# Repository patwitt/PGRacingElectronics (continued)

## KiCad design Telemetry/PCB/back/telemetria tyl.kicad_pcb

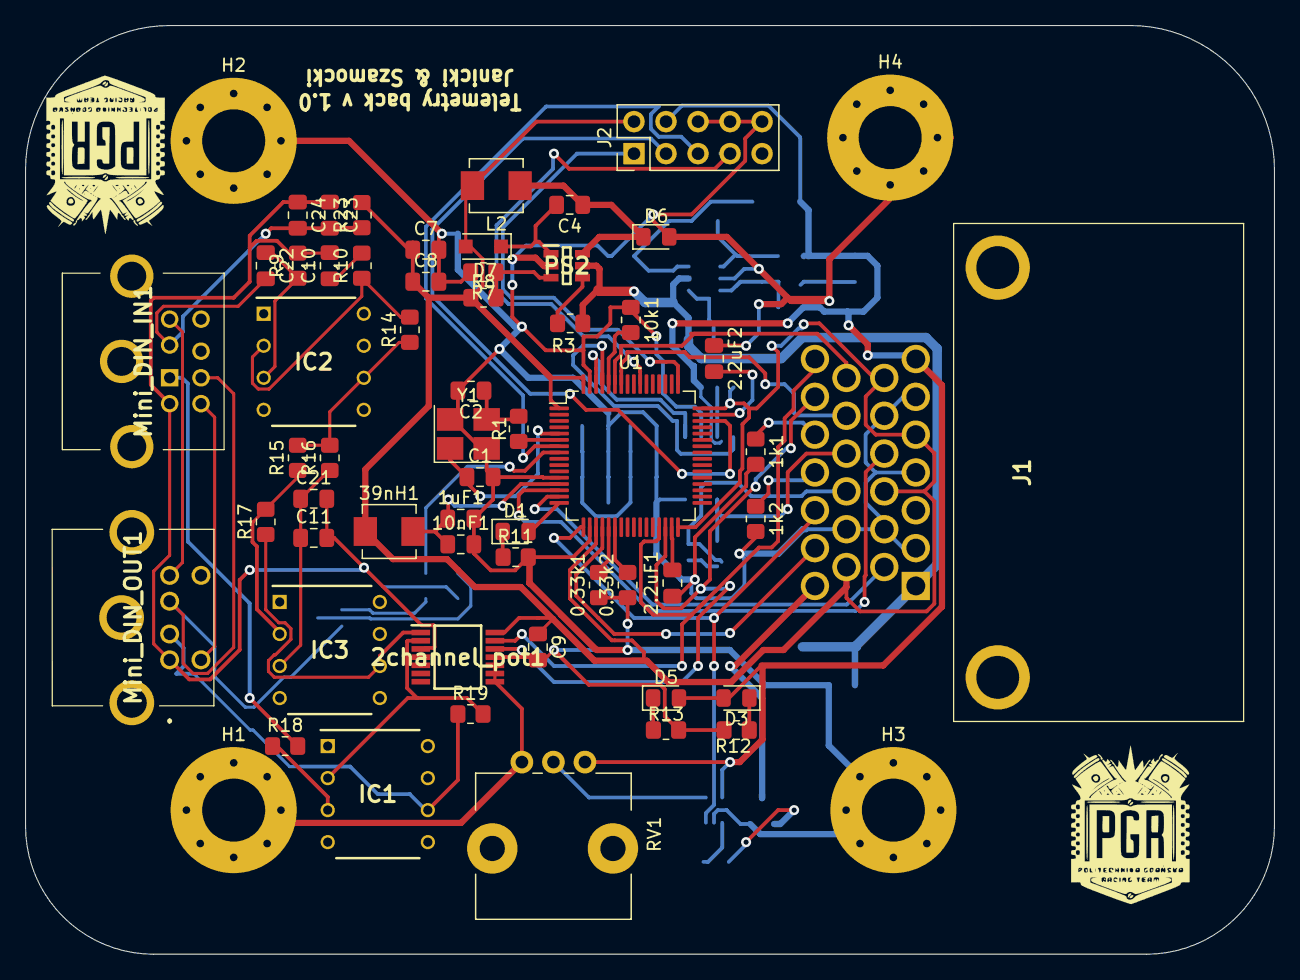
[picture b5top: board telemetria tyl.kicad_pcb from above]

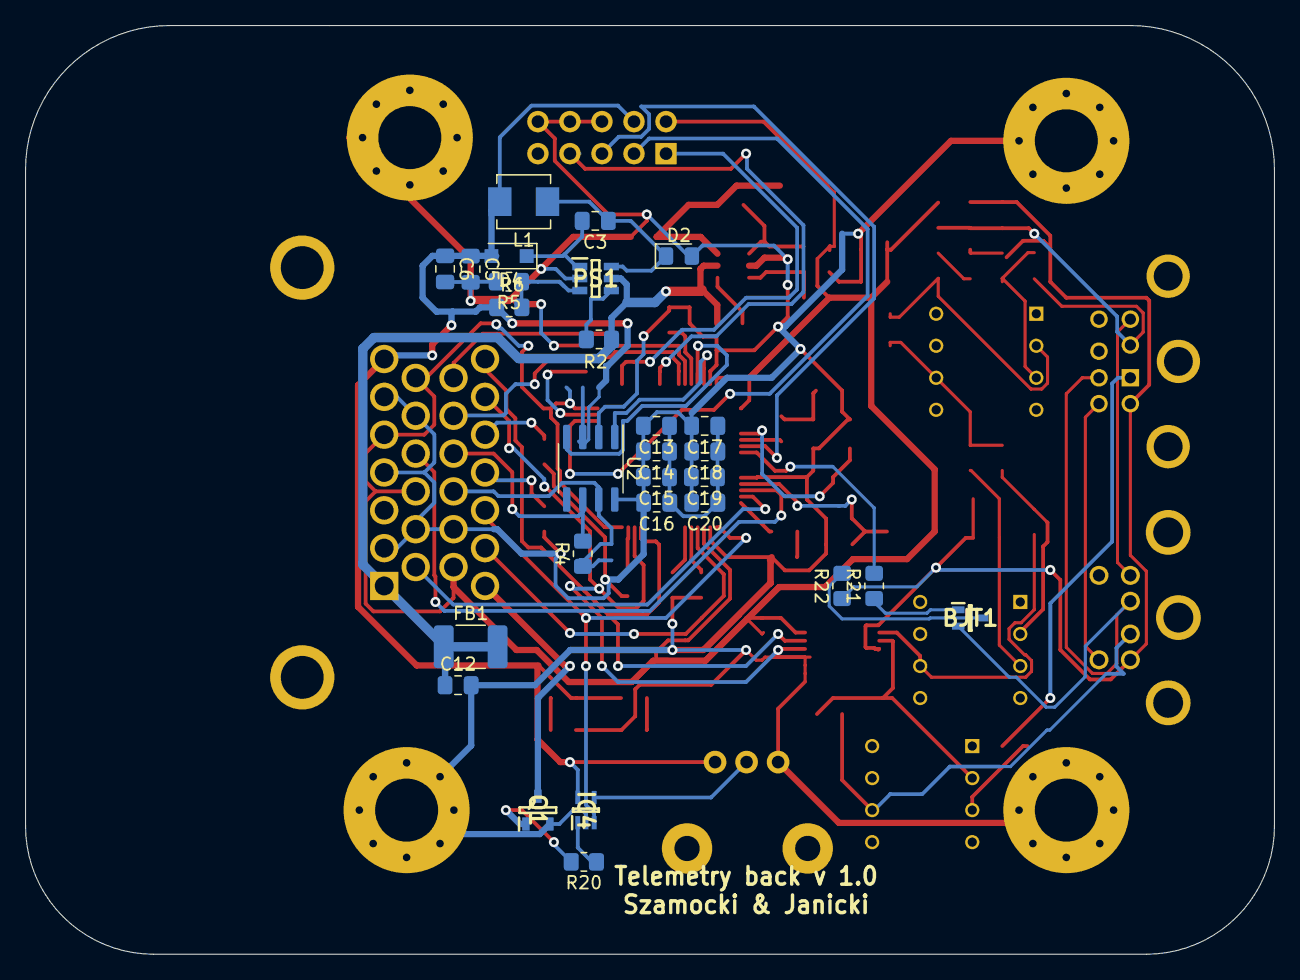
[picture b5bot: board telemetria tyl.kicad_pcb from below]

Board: 2 copper layers, 99.1 x 73.7 mm, 88 parts (28 on the bottom side), 66 nets.

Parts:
0.33k1, 0.33k2, 1k1, 1k2, 10k1: R; R_0805_2012Metric_Pad1.20x1.40mm_HandSolder
1uF1, 10nF1: C1; C_0805_2012Metric_Pad1.18x1.45mm_HandSolder
2.2uF1, 2.2uF2: C_Small; C_0805_2012Metric_Pad1.18x1.45mm_HandSolder
2channel_pot1: MAX5478EUD+T; SOP65P640X110-14N
39nH1: 39nH; L_Vishay_IHLP-1616
BJT1: BC846BW,115; SOT65P210X110-3N
C1, C2: 1uF; C_0805_2012Metric_Pad1.18x1.45mm_HandSolder
C3, C4, C12, C13, C14, C15, C16, C17, C18, C19, C20: 100nF; C_0805_2012Metric_Pad1.18x1.45mm_HandSolder
C5, C6, C7, C8, C24: 10uF; C_0805_2012Metric_Pad1.18x1.45mm_HandSolder
C9: 0.1uF; C_0805_2012Metric_Pad1.18x1.45mm_HandSolder
C10, C11, C21, C22: C; C_0805_2012Metric_Pad1.18x1.45mm_HandSolder
C23: ?; C_0805_2012Metric_Pad1.18x1.45mm_HandSolder
D1, D3, D5: LED_5V; D_0805_2012Metric_Pad1.15x1.40mm_HandSolder
D2, D6: D_Schottky; D_0805_2012Metric_Pad1.15x1.40mm_HandSolder
D4, D7: 1N4148; D_SOD-123F
FB1: Ferrite_Bead; C_1812_4532Metric_Pad1.57x3.40mm_HandSolder
H1, H2, H3, H4: MountingHole_Pad; MountingHole_5mm_Pad_Via
IC1, IC2, IC3: LM741CN_NOPB; DIP794W53P254L959H508Q8N
IC4: NCX2200GW,125; NCX2200GW
J1: Conn_01x26_Male; 64734231
J2: Conn_02x05_Odd_Even; PinHeader_2x05_P2.54mm_Vertical
L1, L2: 10uH; L_Vishay_IHLP-1616
Mini_DIN_IN1: 5749268-1; 57492681
Mini_DIN_OUT1: 5750071-1; 57500711
PS1, PS2: MP2359DT-LF-P; SOT95P280X145-6N
Q1: PMV280ENEAR
R1: R_Small; R_0805_2012Metric_Pad1.20x1.40mm_HandSolder
R2, R3: 100k; R_0805_2012Metric_Pad1.20x1.40mm_HandSolder
R4: 120; R_0805_2012Metric_Pad1.20x1.40mm_HandSolder
R5, R6, R7, R8, R10, R11, R12, R13, R14, R15, R16, R17, R18, R23: R; R_0805_2012Metric_Pad1.20x1.40mm_HandSolder
R9: 1M; R_0805_2012Metric_Pad1.20x1.40mm_HandSolder
R19: R?; R_0805_2012Metric_Pad1.20x1.40mm_HandSolder
R20: 3.3k; R_0805_2012Metric_Pad1.20x1.40mm_HandSolder
R21: 4.7k; R_0805_2012Metric_Pad1.20x1.40mm_HandSolder
R22: 1k; R_0805_2012Metric_Pad1.20x1.40mm_HandSolder
RV1: R_POT; Potentiometer_Alps_RK09L_Single_Vertical
U1: STM32F405RGTx; LQFP-64_10x10mm_P0.5mm
U2: MCP2561-E-SN; SOIC-8_3.9x4.9mm_P1.27mm
Y1: Crystal_GND24_Small; Crystal_SMD_3225-4Pin_3.2x2.5mm_HandSoldering

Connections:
12C1_SCL: J1.18, U1.58
12C2_SDA: 2channel_pot1.12, J1.21, U1.30
+3.3VA: 1uF1.1, 10nF1.1, 39nH1.2, U1.13
+3V3: 2channel_pot1.14, 39nH1.1, C7.1, C8.1, C9.1, C13.1, C14.1, C15.1, C16.1, C17.1, C18.1, C19.1, C20.1, D7.2, J1.5, J1.8, J1.11, J1.14, J2.2, L2.2, R8.1, R23.2, U1.1, U1.19, U1.32, U1.48, U1.64
+5V: C5.1, C6.1, D3.2, D4.2, D5.2, IC4.5, J1.7, J2.4, L1.2, R6.1, RV1.3, U2.3
+12V: C12.1, FB1.1, FB1.2, J1.1, PS1.5, PS2.5, R2.1, R3.1
ADC1_IN0_AMORKI: J1.10, U1.14
ADC2_IN1_AMORKI: J1.13, U1.15
BREAK_PRESSURE_0: IC4.3, J1.24, U1.17
BREAK_PRESSURE_ADC: J1.25, U1.20
CAN1_RX: U1.61, U2.4
CAN1_TX: U1.62, U2.1
CAN_H1: J1.16, R4.1, U2.7
CAN_L1: J1.17, R4.2, U2.6
GND: 0.33k1.1, 0.33k2.1, 1k1.2, 1k2.2, 1uF1.2, 2.2uF1.1, 2.2uF2.1, 2channel_pot1.8, 2channel_pot1.9, 2channel_pot1.10, 2channel_pot1.11, 10k1.1, 10nF1.2, C1.2, C2.2, C5.2, C6.2, C7.2, C8.2, C9.2, C12.2, C13.2, C14.2, C15.2, C16.2, C17.2, C18.2, C19.2, C20.2, D2.2, D6.2, H1.1, H2.1, H3.1, H4.1, IC4.2, J1.2, J1.4, J1.6, J1.9, J1.12, J1.15, J2.6, J2.8, J2.10, PS1.2, PS2.2, Q1.2, R5.2, R7.2, R11.2, R12.2, R13.2, RV1.1, U1.12, U1.18, U1.63, U2.2, U2.8, Y1.2, Y1.4
GND_MIC&ANC: 2channel_pot1.3, C10.2, C11.2, C21.2, C23.1, C24.1, Mini_DIN_IN1.3, Mini_DIN_OUT1.3, R9.2, R22.1
GND_SPK: BJT1.2, Mini_DIN_IN1.4, Mini_DIN_OUT1.2
I2C1_SDA: J1.19, U1.59
I2C2_SCL: 2channel_pot1.13, J1.20, U1.29
LED_GND: J1.26, Q1.3
LED_STATUS: D1.2, U1.16
NRST: J2.5, U1.7
unnamed: 2.2uF1.2, U1.31
unnamed: 2.2uF2.2, U1.47
unnamed: 2channel_pot1.1, IC3.6, R17.1
unnamed: 2channel_pot1.2, IC1.2, R19.2
unnamed: 10k1.2, U1.60
unnamed: BJT1.1, R21.1
unnamed: BJT1.3, R22.2
unnamed: C2.1, R1.2, Y1.3
unnamed: C3.1, D2.1, L1.1, PS1.6
unnamed: C3.2, D4.1, PS1.1
unnamed: C4.1, D6.1, L2.1, PS2.6
unnamed: C4.2, D7.1, PS2.1
unnamed: C10.1, R10.2
unnamed: C11.1, C21.1, IC3.3, R16.1
unnamed: C22.1, IC2.3, R9.1
unnamed: D1.1, R11.1
unnamed: D3.1, R12.1
unnamed: D5.1, R13.1
unnamed: IC1.3, R18.1
unnamed: IC2.2, R10.1, R14.2
unnamed: IC2.6, R14.1, R15.2, R16.2
unnamed: IC3.2, R15.1, R17.2
unnamed: IC4.1, R20.1
unnamed: IC4.4, RV1.2
unnamed: PS1.3, R5.1, R6.2
unnamed: PS1.4, R2.2
unnamed: PS2.3, R7.1, R8.2
unnamed: PS2.4, R3.2
unnamed: Q1.1, R20.2
PTT: R21.2, U1.8
RCC_OSC_IN: C1.1, U1.5, Y1.1
RCC_OSC_OUT: R1.1, U1.6
SPK+: Mini_DIN_IN1.5, Mini_DIN_OUT1.4
SWCLK: J2.1, U1.49
SWDIO: J2.3, U1.46
SWO: J2.7, U1.55
TIM2_ETR: 0.33k1.2, U1.21
TIM3_ETR: 0.33k2.2, U1.22
TX_DATA: Mini_DIN_IN1.6, Mini_DIN_OUT1.5
VSS_IN_1: 1k1.1, J1.22
VSS_IN_2: 1k2.1, J1.23
V_ANC: C22.2, C23.2, C24.2, Mini_DIN_IN1.2, R23.1
V_MIC: Mini_DIN_IN1.1, R18.2
V_OUT: IC1.6, Mini_DIN_OUT1.1, R19.1

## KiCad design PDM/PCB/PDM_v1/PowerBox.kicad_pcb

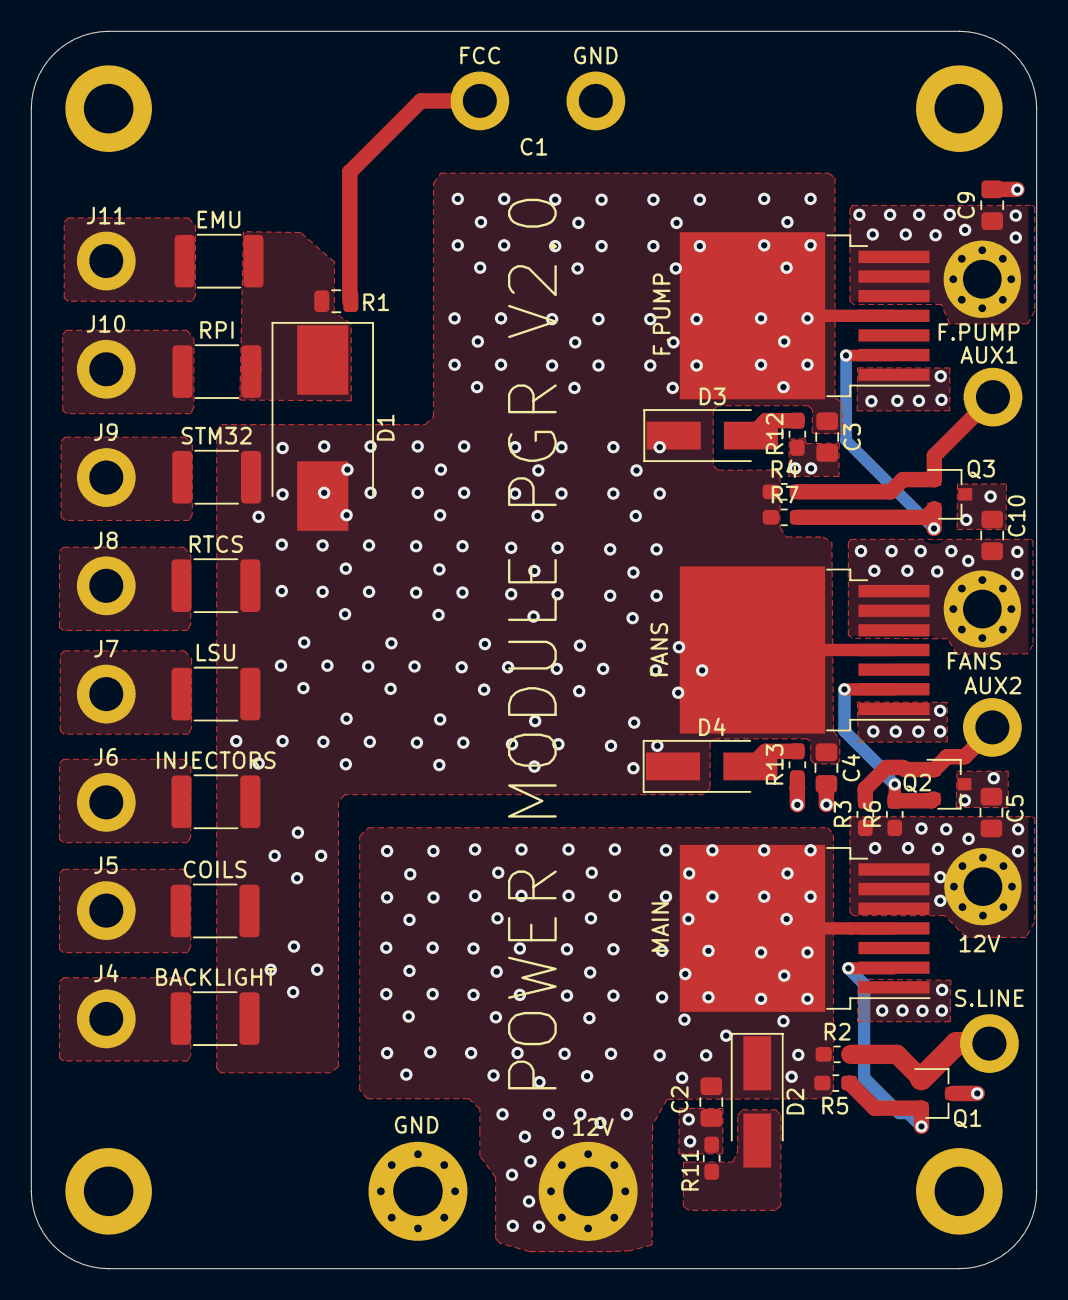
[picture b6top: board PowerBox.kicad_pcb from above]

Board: 4 copper layers, 65.0 x 80.0 mm, 55 parts (0 on the bottom side), 24 nets.

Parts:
12V: 85 K1 (starter); MountingHole_2.5mm_Pad_Via
AUX1: EMU PIN 21 GN(AUX1); MountingHole_2.2mm_M2_DIN965_Pad
AUX2: EMU PIN 13 GN (AUX2); MountingHole_2.2mm_M2_DIN965_Pad
BACKLIGHT: 2; Fuse_1812_4532Metric_Pad1.30x3.40mm_HandSolder
C1: 0.2F; Kondensator
C2, C3, C4: 100nF; C_0805_2012Metric_Pad1.15x1.40mm_HandSolder
C5, C9, C10: 10nF; C_0805_2012Metric_Pad1.15x1.40mm_HandSolder
COILS: 15; Fuse_1812_4532Metric_Pad1.30x3.40mm_HandSolder
D1: D; D_SMC_Handsoldering
D2, D3, D4: D_TVS_ALT; D_SMA_Handsoldering
EMU: 3; Fuse_1812_4532Metric_Pad1.30x3.40mm_HandSolder
F.PUMP: FUEL PUMP; MountingHole_2.5mm_Pad_Via
F.PUMP#2: BTS50010-1TAE; TO-263-7_TabPin4
FANS: FANS; MountingHole_2.5mm_Pad_Via
FANS#2: BTS50010-1TAE; TO-263-7_TabPin4
H1, H2, H3, H4: MountingHole; MountingHole_3.2mm_M3_DIN965_Pad
INJECTORS: 15; Fuse_1812_4532Metric_Pad1.30x3.40mm_HandSolder
J1: 12V BAT; MountingHole_3.2mm_M3_Pad_Via
J4: BACK LIGHT; MountingHole_2.2mm_M2_DIN965_Pad
J5: COILS; MountingHole_2.2mm_M2_DIN965_Pad
J6: INJECTORS; MountingHole_2.2mm_M2_DIN965_Pad
J7: LSU 4.9; MountingHole_2.2mm_M2_DIN965_Pad
J8: RACE TCS; MountingHole_2.2mm_M2_DIN965_Pad
J9: STM BOX; MountingHole_2.2mm_M2_DIN965_Pad
J10: RASPBERRY PI; MountingHole_2.2mm_M2_DIN965_Pad
J11: EMU; MountingHole_2.2mm_M2_DIN965_Pad
J16: GND; MountingHole_3.2mm_M3_Pad_Via
LSU: 3; Fuse_1812_4532Metric_Pad1.30x3.40mm_HandSolder
MAIN: BTS50010-1TAE; TO-263-7_TabPin4
Q1, Q2, Q3: Q_NPN_BCE; SOT-23
R1: 0.1; R_0805_2012Metric
R2, R3, R4: 22k; R_0603_1608Metric_Pad1.05x0.95mm_HandSolder
R5, R6, R7: 10k; R_0603_1608Metric_Pad1.05x0.95mm_HandSolder
R11, R12, R13: 1R; R_0603_1608Metric_Pad1.05x0.95mm_HandSolder
RPI: 5; Fuse_1812_4532Metric_Pad1.30x3.40mm_HandSolder
RTCS: Fuse; Fuse_1812_4532Metric_Pad1.30x3.40mm_HandSolder
S.LINE: SAFETY SYSTEM; MountingHole_2.2mm_M2_DIN965_Pad
STM32: 7.5; Fuse_1812_4532Metric_Pad1.30x3.40mm_HandSolder

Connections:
12V_BAT: C2.1, D2.1, J1.1, MAIN.4, R2.1, R5.1
12V_OUT1: 12V.1, BACKLIGHT.2, C3.1, C4.1, C5.1, COILS.2, D1.2, D3.1, D4.1, F.PUMP#2.4, FANS#2.4, INJECTORS.2, LSU.2, MAIN.5, MAIN.6, MAIN.7, R3.1, R4.1, R6.1, R7.1, RTCS.2, STM32.2
GND: C1.2, C2.2, C3.2, C4.2, C5.2, C9.2, C10.2, F.PUMP#2.1, FANS#2.1, J16.1, MAIN.1, Q1.3, Q2.3, Q3.3, R11.1, R12.1, R13.1
IN_1: MAIN.2, Q1.2, R5.2
IN_2: FANS#2.2, Q2.2, R6.2
IN_3: F.PUMP#2.2, Q3.2, R7.2
unnamed: C1.1, R1.2
unnamed: C9.1, F.PUMP.1, F.PUMP#2.5, F.PUMP#2.6, F.PUMP#2.7
unnamed: C10.1, FANS.1, FANS#2.5, FANS#2.6, FANS#2.7
unnamed: D1.1, EMU.2, R1.1, RPI.2
unnamed: D2.2, R11.2
unnamed: D3.2, R12.2
unnamed: D4.2, R13.2
unnamed: BACKLIGHT.1, J4.1
unnamed: COILS.1, J5.1
unnamed: INJECTORS.1, J6.1
unnamed: J7.1, LSU.1
unnamed: J8.1, RTCS.1
unnamed: J9.1, STM32.1
unnamed: J10.1, RPI.1
unnamed: EMU.1, J11.1
unnamed: AUX1.1, Q3.1, R4.2
unnamed: Q1.1, R2.2, S.LINE.1
unnamed: AUX2.1, Q2.1, R3.2

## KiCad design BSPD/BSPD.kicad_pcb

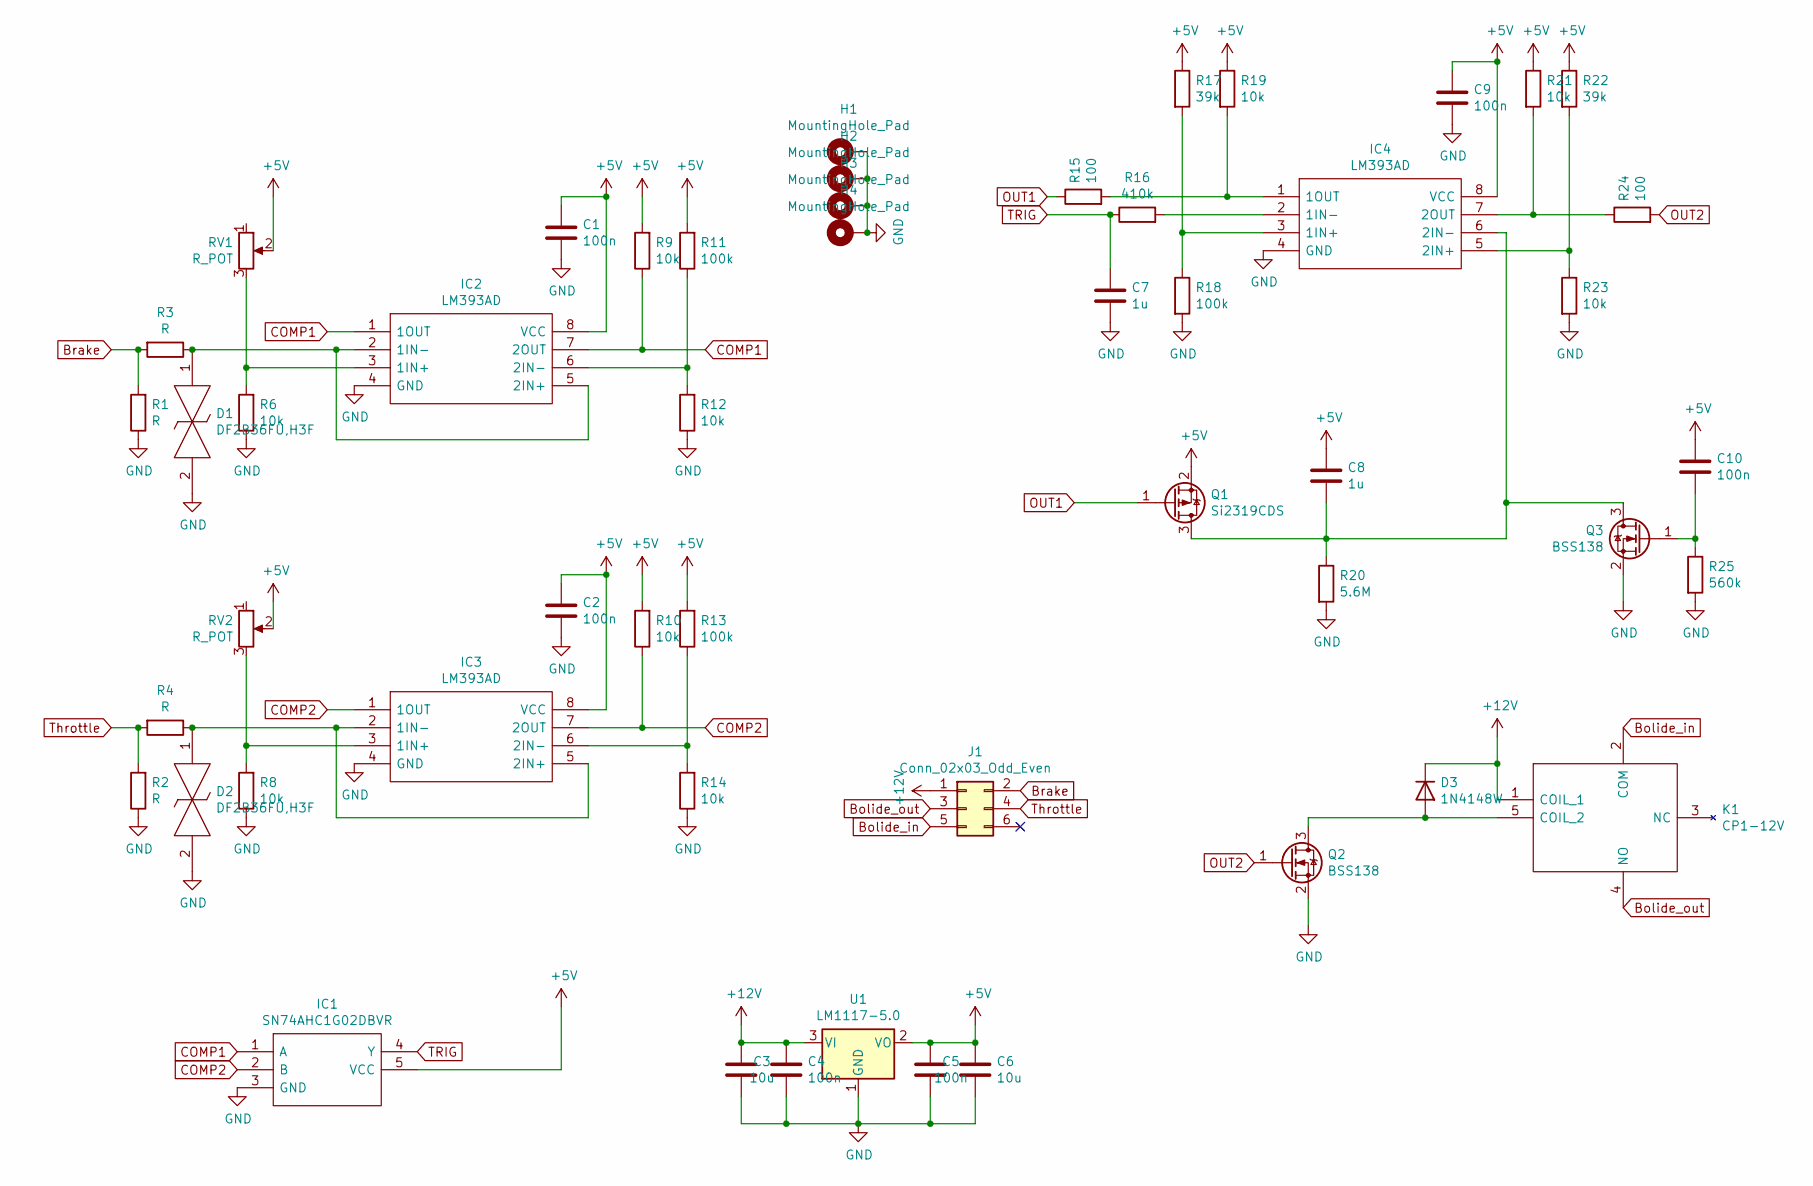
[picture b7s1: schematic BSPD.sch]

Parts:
C1, C2, C4, C5, C9, C10: 100n; C_0805_2012Metric
C3, C6: 10u; C_0805_2012Metric
C7, C8: 1u; C_0805_2012Metric
D1, D2: DF2B36FU,H3F; 1SS357TPH3F; Mouser Part Number 757-DF2B36FUH3F
D3: 1N4148W; D_SOD-123
H1, H2, H3, H4: MountingHole_Pad; MountingHole_2.2mm_M2_Pad_Via
IC1: SN74AHC1G02DBVR; SOT95P280X145-5N; Mouser Part Number 595-SN74AHC1G02DBVR
IC2, IC3, IC4: LM393AD; SOIC127P600X175-8N; Mouser Part Number 595-LM393AD
J1: Conn_02x03_Odd_Even; PinHeader_2x03_P2.54mm_Vertical
K1: CP1-12V; CP1FORMC_1; Mouser Part Number 769-CP1-12V
Q1: Si2319CDS; SOT-23
Q2, Q3: BSS138; SOT-23
R1, R2, R3, R4: R; R_0805_2012Metric
R6, R8, R9, R10, R12, R14, R19, R21, R23: 10k; R_0805_2012Metric
R11, R13, R18: 100k; R_0805_2012Metric
R15, R24: 100; R_0805_2012Metric
R16: 410k; R_0805_2012Metric
R17, R22: 39k; R_0805_2012Metric
R20: 5.6M; R_0805_2012Metric
R25: 560k; R_0805_2012Metric
RV1, RV2: R_POT; 64XK
U1: LM1117-5.0; SOT-223

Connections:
+5V: C1.1, C2.1, C5.1, C6.1, C8.1, C9.1, C10.1, IC1.5 (VCC), IC2.8 (VCC), IC3.8 (VCC), IC4.8 (VCC), Q1.2 (S), R9.2, R10.2, R11.2, R13.2, R17.1, R19.1, R21.1, R22.1, RV1.2, RV2.2, U1.2 (VO)
+12V: C3.1, C4.1, D3.1 (K), J1.1, K1.1 (COIL_1), U1.3 (VI)
Bolide_in: J1.5, K1.2 (COM)
Bolide_out: J1.3, K1.4 (NO)
Brake: J1.2, R1.2, R3.2
COMP1: IC1.1 (A), IC2.1 (1OUT), IC2.7 (2OUT), R9.1
COMP2: IC1.2 (B), IC3.1 (1OUT), IC3.7 (2OUT), R10.1
GND: C1.2, C2.2, C3.2, C4.2, C5.2, C6.2, C7.2, C9.2, D1.2, D2.2, H1.1, H2.1, H3.1, H4.1, IC1.3 (GND), IC2.4 (GND), IC3.4 (GND), IC4.4 (GND), Q2.2 (S), Q3.2 (S), R1.1, R2.1, R6.1, R8.1, R12.1, R14.1, R18.2, R20.2, R23.2, R25.2, U1.1 (GND)
unnamed: C8.2, IC4.6 (2IN-), Q1.3 (D), Q3.3 (D), R20.1
unnamed: C10.2, Q3.1 (G), R25.1
unnamed: D1.1, IC2.2 (1IN-), IC2.5 (2IN+), R3.1
unnamed: D2.1, IC3.2 (1IN-), IC3.5 (2IN+), R4.1
unnamed: D3.2 (A), K1.5 (COIL_2), Q2.3 (D)
unnamed: IC2.3 (1IN+), R6.2, RV1.3
unnamed: IC2.6 (2IN-), R11.1, R12.2
unnamed: IC3.3 (1IN+), R8.2, RV2.3
unnamed: IC3.6 (2IN-), R13.1, R14.2
unnamed: IC4.1 (1OUT), R15.2, R19.2
unnamed: IC4.2 (1IN-), R16.2
unnamed: IC4.3 (1IN+), R17.2, R18.1
unnamed: IC4.5 (2IN+), R22.2, R23.1
unnamed: IC4.7 (2OUT), R21.2, R24.1
OUT1: Q1.1 (G), R15.1
OUT2: Q2.1 (G), R24.2
TRIG: C7.1, IC1.4 (Y), R16.1
Throttle: J1.4, R2.2, R4.2

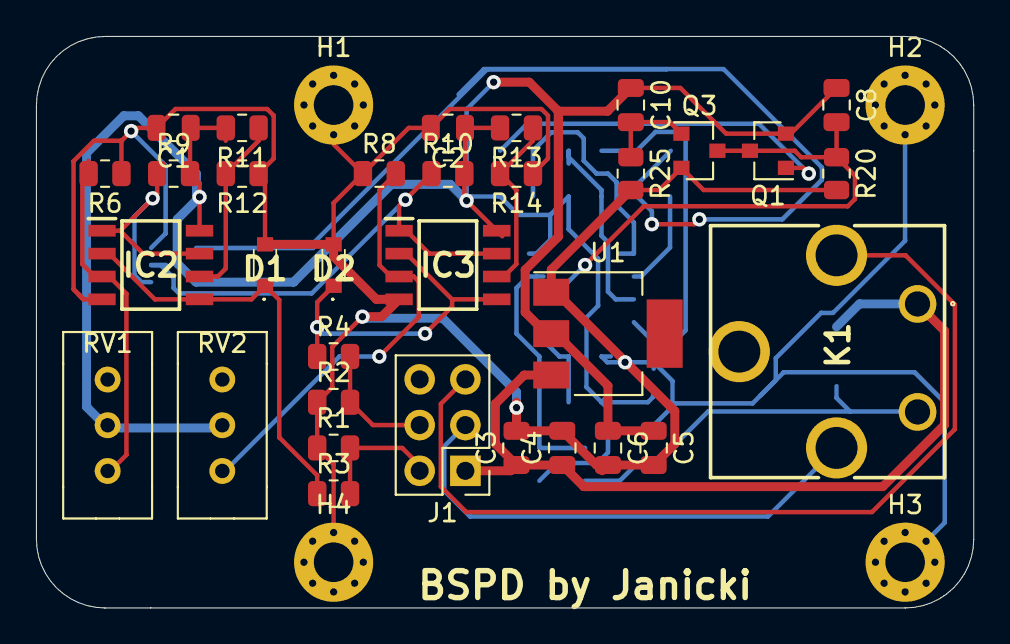
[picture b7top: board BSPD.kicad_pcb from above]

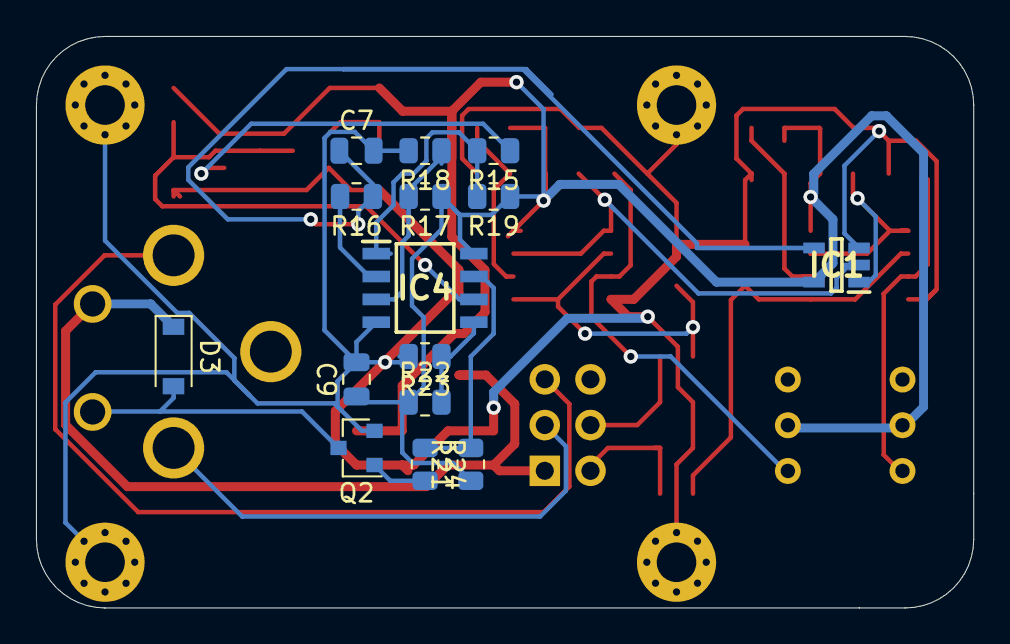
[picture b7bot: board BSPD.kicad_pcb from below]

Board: 2 copper layers, 52.1 x 31.8 mm, 52 parts (15 on the bottom side), 26 nets.

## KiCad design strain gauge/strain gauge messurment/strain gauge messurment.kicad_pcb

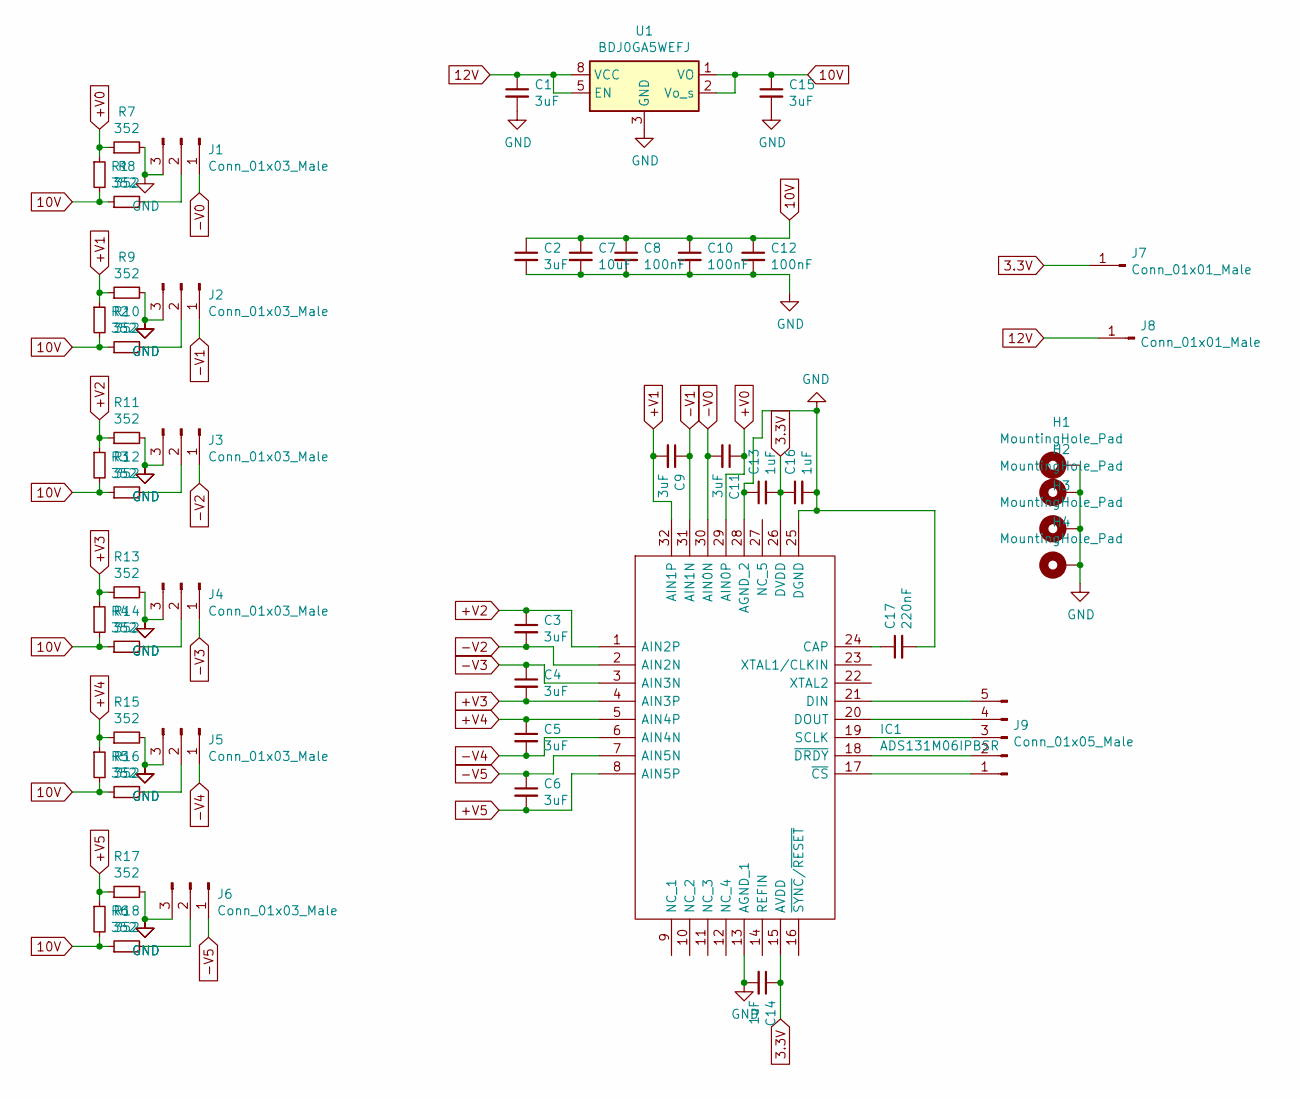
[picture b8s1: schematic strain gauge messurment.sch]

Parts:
C1, C2, C3, C4, C5, C6, C9, C11, C15: 3uF; C_0805_2012Metric_Pad1.18x1.45mm_HandSolder
C7: 10uF; C_0805_2012Metric_Pad1.18x1.45mm_HandSolder
C8, C10, C12: 100nF; C_0805_2012Metric_Pad1.18x1.45mm_HandSolder
C13, C14, C16: 1uF; C_0805_2012Metric_Pad1.18x1.45mm_HandSolder
C17: 220nF; C_0805_2012Metric_Pad1.18x1.45mm_HandSolder
H1, H2, H3, H4: MountingHole_Pad; MountingHole_5mm_Pad_Via
IC1: ADS131M06IPBSR; Manufacturer_Part_Number ADS131M06IPBSR; Mouser Part Number 595-ADS131M06IPBSR
J1, J2, J3, J4, J5, J6: Conn_01x03_Male; PinSocket_1x03_P2.54mm_Vertical
J7, J8: Conn_01x01_Male; PinHeader_1x01_P2.54mm_Vertical
J9: Conn_01x05_Male; PinSocket_1x05_P2.54mm_Vertical
R1, R2, R3, R4, R5, R6, R7, R8, R9, R10, R11, R12, R13, R14, R15, R16, R17, R18: 352; R_0805_2012Metric_Pad1.20x1.40mm_HandSolder
U1: BDJ0GA5WEFJ; HTSOP-8-1EP_3.9x4.9mm_P1.27mm_EP2.4x3.2mm

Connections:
3.3V: C13.2, C14.1, C16.1, IC1.15 (AVDD), IC1.26 (DVDD), J7.1
10V: C2.1, C7.1, C8.1, C10.1, C12.1, C15.1, R1.2, R2.2, R3.2, R4.2, R5.2, R6.2, R8.1, R10.1, R12.1, R14.1, R16.1, R18.1, U1.1 (VO), U1.2 (Vo_s)
12V: C1.1, J8.1, U1.5 (EN), U1.8 (VCC)
+V0: C11.1, IC1.29 (AIN0P), R1.1, R7.1
+V1: C9.2, IC1.32 (AIN1P), R2.1, R9.1
+V2: C3.1, IC1.1 (AIN2P), R3.1, R11.1
+V3: C4.2, IC1.4 (AIN3P), R4.1, R13.1
+V4: C5.1, IC1.5 (AIN4P), R5.1, R15.1
+V5: C6.2, IC1.8 (AIN5P), R6.1, R17.1
-V0: C11.2, IC1.30 (AIN0N), J1.1
-V1: C9.1, IC1.31 (AIN1N), J2.1
-V2: C3.2, IC1.2 (AIN2N), J3.1
-V3: C4.1, IC1.3 (AIN3N), J4.1
-V4: C5.2, IC1.6 (AIN4N), J5.1
-V5: C6.1, IC1.7 (AIN5N), J6.1
GND: C1.2, C2.2, C7.2, C8.2, C10.2, C12.2, C13.1, C14.2, C15.2, C16.2, C17.2, H1.1, H2.1, H3.1, H4.1, IC1.13 (AGND_1), IC1.25 (DGND), IC1.28 (AGND_2), J1.3, J2.3, J3.3, J4.3, J5.3, J6.3, R7.2, R9.2, R11.2, R13.2, R15.2, R17.2, U1.3 (GND), U1.4 (GND), U1.6 (GND), U1.7 (GND), U1.9 (GND)
unnamed: C17.1, IC1.24 (CAP)
unnamed: IC1.17 (~CS), J9.1
unnamed: IC1.18 (~DRDY), J9.2
unnamed: IC1.19 (SCLK), J9.3
unnamed: IC1.20 (DOUT), J9.4
unnamed: IC1.21 (DIN), J9.5
unnamed: J1.2, R8.2
unnamed: J2.2, R10.2
unnamed: J3.2, R12.2
unnamed: J4.2, R14.2
unnamed: J5.2, R16.2
unnamed: J6.2, R18.2

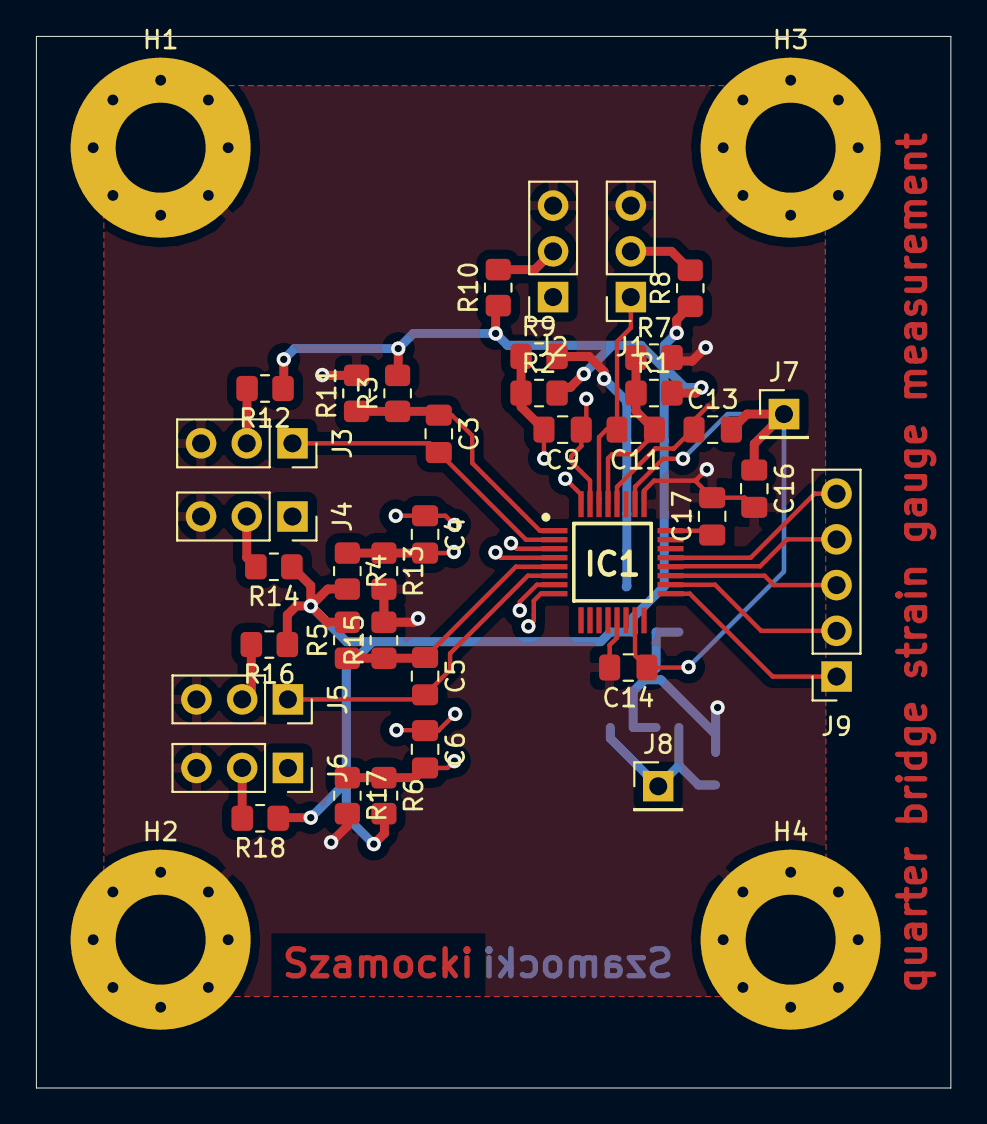
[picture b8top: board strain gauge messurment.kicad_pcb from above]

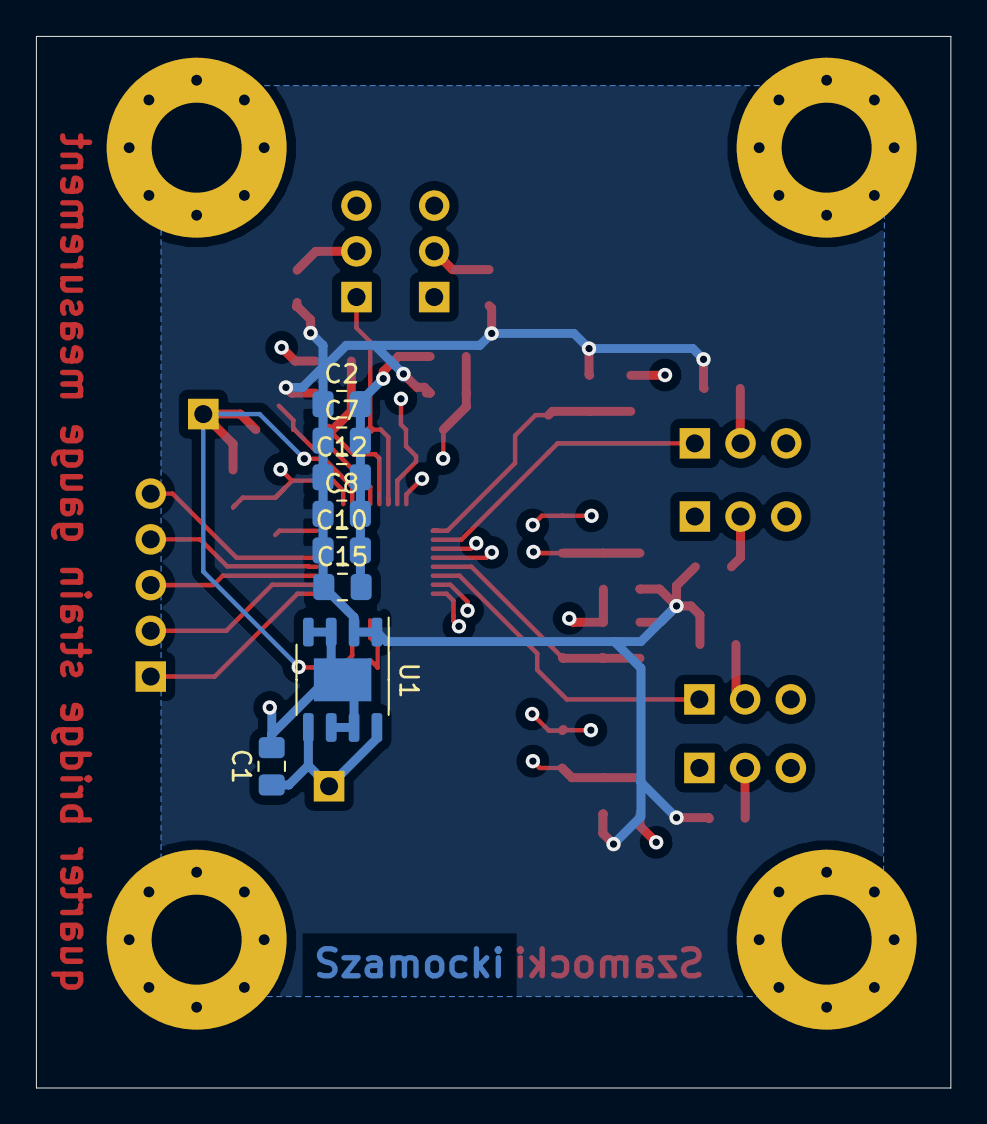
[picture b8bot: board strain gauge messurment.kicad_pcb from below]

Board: 4 copper layers, 50.8 x 58.4 mm, 50 parts (8 on the bottom side), 28 nets.

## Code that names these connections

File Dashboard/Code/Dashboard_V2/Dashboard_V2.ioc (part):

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Mcu.Name=STM32F767ZITx
Mcu.Package=LQFP144
Mcu.UserName=STM32F767ZITx
PA1.Mode=RGB888
PA1.Signal=LTDC_R2
PA10.Mode=RGB888
PA10.Signal=LTDC_B1
PA11.Mode=CAN_Activate
PA11.Signal=CAN1_RX
PA12.Mode=CAN_Activate
PA12.Signal=CAN1_TX
PA13.Mode=Trace_Asynchronous_SW
PA13.Signal=SYS_JTMS-SWDIO
PA14.Mode=Trace_Asynchronous_SW
PA14.Signal=SYS_JTCK-SWCLK
PA2.Mode=RGB888
PA2.Signal=LTDC_R1
PA3.Mode=RGB888
PA3.Signal=LTDC_B5
PA4.Mode=RGB888
PA4.Signal=LTDC_VSYNC
PA5.Mode=RGB888
PA5.Signal=LTDC_R4
PA6.Mode=RGB888
PA6.Signal=LTDC_G2
PA7.Signal=FMC_SDNWE
PB0.Mode=RGB888
PB0.Signal=LTDC_R3
PB1.Mode=RGB888
PB1.Signal=LTDC_R6
PB10.Mode=RGB888
PB10.Signal=LTDC_G4
PB11.Mode=RGB888
PB11.Signal=LTDC_G5
PB12.Mode=CAN_Activate
PB12.Signal=CAN2_RX
PB13.Mode=CAN_Activate
PB13.Signal=CAN2_TX
PB2.Mode=Single Bank 1
PB2.Signal=QUADSPI_CLK
PB3.Mode=Trace_Asynchronous_SW
PB3.Signal=SYS_JTDO-SWO
PB4.Signal=S_TIM3_CH1
PB6.Mode=Single Bank 1
PB6.Signal=QUADSPI_BK1_NCS
PB8.Mode=RGB888
PB8.Signal=LTDC_B6
PB9.Mode=RGB888
PB9.Signal=LTDC_B7
PC0.Mode=RGB888
PC0.Signal=LTDC_R5
PC1.Signal=ADCx_IN11
PC2.Mode=SdramChipSelect1_1
PC2.Signal=FMC_SDNE0
PC3.Mode=SdramChipSelect1_1
PC3.Signal=FMC_SDCKE0
PC6.Mode=RGB888
PC6.Signal=LTDC_HSYNC
PC7.Mode=RGB888
PC7.Signal=LTDC_G6
PC9.Mode=RGB888
PC9.Signal=LTDC_B2
PD0.Signal=FMC_D2_DA2
PD1.Signal=FMC_D3_DA3
PD10.Signal=FMC_D15_DA15
PD12.Signal=S_TIM4_CH1
PD14.Signal=FMC_D0_DA0
PD15.Signal=FMC_D1_DA1
PD3.Mode=RGB888
PD3.Signal=LTDC_G7
PD8.Signal=FMC_D13_DA13
PD9.Signal=FMC_D14_DA14
PE0.Signal=FMC_NBL0
PE1.Signal=FMC_NBL1
PE10.Signal=FMC_D7_DA7
PE11.Signal=FMC_D8_DA8
PE12.Signal=FMC_D9_DA9
PE13.Signal=FMC_D10_DA10
PE14.Signal=FMC_D11_DA11
PE15.Signal=FMC_D12_DA12
PE4.Mode=RGB888
PE4.Signal=LTDC_B0
PE5.Mode=RGB888
PE5.Signal=LTDC_G0
PE6.Mode=RGB888
PE6.Signal=LTDC_G1
PE7.Signal=FMC_D4_DA4
PE8.Signal=FMC_D5_DA5
PE9.Signal=FMC_D6_DA6
PF0.Signal=FMC_A0
PF1.Signal=FMC_A1
PF10.Mode=RGB888
PF10.Signal=LTDC_DE
PF11.Signal=FMC_SDNRAS
PF12.Signal=FMC_A6
PF13.Signal=FMC_A7
PF14.Signal=FMC_A8
PF15.Signal=FMC_A9
PF2.Signal=FMC_A2
PF3.Signal=FMC_A3
PF4.Signal=FMC_A4
PF5.Signal=FMC_A5
PF6.Mode=Single Bank 1
PF6.Signal=QUADSPI_BK1_IO3
PF7.Mode=Single Bank 1
PF7.Signal=QUADSPI_BK1_IO2
PF8.Mode=Single Bank 1
PF8.Signal=QUADSPI_BK1_IO0
PF9.Mode=Single Bank 1
PF9.Signal=QUADSPI_BK1_IO1
PG0.Signal=FMC_A10
PG10.Mode=RGB888
PG10.Signal=LTDC_G3
PG11.Mode=RGB888
PG11.Signal=LTDC_B3
PG12.Mode=RGB888
PG12.Signal=LTDC_B4
PG13.Mode=RGB888
PG13.Signal=LTDC_R0
PG15.Signal=FMC_SDNCAS
PG4.Signal=FMC_A14_BA0
PG6.Mode=RGB888
PG6.Signal=LTDC_R7
PG7.Mode=RGB888
PG7.Signal=LTDC_CLK
PG8.Signal=FMC_SDCLK
PH0/OSC_IN.Mode=HSE-External-Oscillator
PH0/OSC_IN.Signal=RCC_OSC_IN
PH1/OSC_OUT.Mode=HSE-External-Oscillator
PH1/OSC_OUT.Signal=RCC_OSC_OUT
RCC.HSE_VALUE=25000000
RCC.SYSCLKFreq_VALUE=216000000
RCC.SYSCLKSource=RCC_SYSCLKSOURCE_PLLCLK
board=custom

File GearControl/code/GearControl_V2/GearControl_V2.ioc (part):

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Mcu.Name=STM32F405RGTx
Mcu.Package=LQFP64
Mcu.UserName=STM32F405RGTx
PA1.GPIOParameters=GPIO_PuPd,GPIO_Label,GPIO_Mode
PA1.GPIO_Label=GEAR_SENS
PA1.GPIO_Mode=GPIO_MODE_ANALOG
PA1.GPIO_PuPd=GPIO_NOPULL
PA1.Signal=ADCx_IN1
PA10.GPIOParameters=GPIO_Label
PA10.GPIO_Label=INH1
PA10.Signal=GPIO_Output
PA11.GPIOParameters=GPIO_Label
PA11.GPIO_Label=PWM_H_IN1
PA11.Signal=S_TIM1_CH4
PA13.Mode=Serial_Wire
PA13.Signal=SYS_JTMS-SWDIO
PA14.Mode=Serial_Wire
PA14.Signal=SYS_JTCK-SWCLK
PA2.GPIOParameters=GPIO_Label
PA2.GPIO_Label=LED_STATUS
PA2.Signal=GPIO_Output
PA3.GPIOParameters=GPIO_PuPd,GPIO_Label,GPIO_Mode
PA3.GPIO_Label=IS
PA3.GPIO_Mode=GPIO_MODE_ANALOG
PA3.GPIO_PuPd=GPIO_NOPULL
PA3.Signal=ADCx_IN3
PA5.GPIOParameters=GPIO_Label
PA5.GPIO_Label=TPS_1
PA5.Signal=ADCx_IN5
PA7.GPIOParameters=GPIO_Label
PA7.GPIO_Label=TPS_2
PA7.Signal=ADCx_IN7
PA8.GPIOParameters=GPIO_Label
PA8.GPIO_Label=PWM_H_IN2
PA8.Signal=S_TIM1_CH1
PA9.GPIOParameters=GPIO_Label
PA9.GPIO_Label=INH2
PA9.Signal=GPIO_Output
PB1.GPIOParameters=GPIO_Label
PB1.GPIO_Label=APPS_2
PB1.Signal=ADCx_IN9
PB12.Signal=GPIO_Output
PB14.GPIOParameters=PinState,GPIO_Label
PB14.GPIO_Label=GEAR_CUT
PB14.PinState=GPIO_PIN_SET
PB14.Signal=GPIO_Output
PB3.Signal=S_TIM2_CH2
PB8.Mode=CAN_Activate
PB8.Signal=CAN1_RX
PB9.Mode=CAN_Activate
PB9.Signal=CAN1_TX
PC1.GPIOParameters=GPIO_Label
PC1.GPIO_Label=SW_GEAR_UP
PC1.Signal=GPIO_Input
PC10.GPIOParameters=PinState
PC10.PinState=GPIO_PIN_SET
PC10.Signal=GPIO_Output
PC2.GPIOParameters=GPIO_Label
PC2.GPIO_Label=SW_GEAR_DOWN
PC2.Signal=GPIO_Input
PC5.GPIOParameters=GPIO_Label
PC5.GPIO_Label=APPS_1
PC5.Signal=ADCx_IN15
PC6.GPIOParameters=GPIO_Label
PC6.GPIO_Label=PWM_CLUTCH
PC6.Signal=S_TIM3_CH1
PC8.GPIOParameters=GPIO_Label
PC8.GPIO_Label=PWM_GEAR
PC8.Signal=S_TIM3_CH3
PC9.GPIOParameters=GPIO_Label
PC9.GPIO_Label=OE
PC9.Signal=GPIO_Output
PH0-OSC_IN.Mode=HSE-External-Oscillator
PH0-OSC_IN.Signal=RCC_OSC_IN
PH1-OSC_OUT.Mode=HSE-External-Oscillator
PH1-OSC_OUT.Signal=RCC_OSC_OUT
RCC.HSE_VALUE=16000000
RCC.SYSCLKFreq_VALUE=168000000
RCC.SYSCLKSource=RCC_SYSCLKSOURCE_PLLCLK
board=custom

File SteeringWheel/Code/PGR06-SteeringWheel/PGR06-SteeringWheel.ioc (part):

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Mcu.Name=STM32F405RGTx
Mcu.Package=LQFP64
Mcu.UserName=STM32F405RGTx
PA0-WKUP.GPIOParameters=GPIO_Label
PA0-WKUP.GPIO_Label=ROT_UNI
PA0-WKUP.Signal=ADCx_IN0
PA1.GPIOParameters=GPIO_Label
PA1.GPIO_Label=ROT_SCR
PA1.Signal=ADCx_IN1
PA11.Mode=CAN_Activate
PA11.Signal=CAN1_RX
PA12.Mode=CAN_Activate
PA12.Signal=CAN1_TX
PA2.GPIOParameters=GPIO_Label
PA2.GPIO_Label=LED_STATUS
PA2.Signal=GPIO_Output
PA5.Signal=GPIO_Output
PA6.Signal=GPIO_Output
PA7.Signal=GPIO_Output
PA8.Signal=S_TIM1_CH1
PA9.Signal=S_TIM1_CH2
PB0.GPIOParameters=GPIO_Label
PB0.GPIO_Label=BTN_CLCH
PB0.Signal=GPIO_Input
PB1.GPIOParameters=GPIO_Label
PB1.GPIO_Label=BTN_UNI1
PB1.Signal=GPIO_Input
PB10.GPIOParameters=GPIO_Label
PB10.GPIO_Label=BTN_UNI2
PB10.Signal=GPIO_Output
PB12.Mode=CAN_Activate
PB12.Signal=CAN2_RX
PB13.Mode=CAN_Activate
PB13.Signal=CAN2_TX
PB2.GPIOParameters=GPIO_Label
PB2.GPIO_Label=BTN_DRS
PB2.Signal=GPIO_Input
PB5.GPIOParameters=GPIO_PuPd,GPIO_Label
PB5.GPIO_Label=I2C_RESET
PB5.GPIO_PuPd=GPIO_PULLUP
PB5.Signal=GPIO_Output
PB6.Mode=I2C
PB6.Signal=I2C1_SCL
PB7.Mode=I2C
PB7.Signal=I2C1_SDA
PC11.Signal=GPXTI11
PC4.GPIOParameters=GPIO_Label
PC4.GPIO_Label=BTN_SCR
PC4.Signal=GPIO_Input
PC5.GPIOParameters=GPIO_Label
PC5.GPIO_Label=BTN_PTT
PC5.Signal=GPIO_Input
RCC.HSE_VALUE=25000000
RCC.SYSCLKFreq_VALUE=16000000
board=custom

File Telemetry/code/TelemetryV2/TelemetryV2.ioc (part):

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Mcu.Name=STM32F767ZITx
Mcu.Package=LQFP144
Mcu.UserName=STM32F767ZITx
PA0/WKUP.Signal=ADCx_IN0
PA1.Signal=ADCx_IN1
PA10.GPIOParameters=GPIO_Label
PA10.GPIO_Label=USB_SW
PA10.Signal=GPIO_Output
PA11.Mode=Host_Only
PA11.Signal=USB_OTG_FS_DM
PA12.Mode=Host_Only
PA12.Signal=USB_OTG_FS_DP
PA2.Signal=ADCx_IN2
PA3.Signal=ADCx_IN3
PA5.Signal=S_TIM2_CH1_ETR
PA8.Mode=I2C
PA8.Signal=I2C3_SCL
PB1.GPIOParameters=GPIO_Label
PB1.GPIO_Label=ABS_SPARE2
PB1.Signal=S_TIM3_CH4
PB10.Mode=I2C
PB10.Signal=I2C2_SCL
PB11.Mode=I2C
PB11.Signal=I2C2_SDA
PB12.Mode=CAN_Activate
PB12.Signal=CAN2_RX
PB13.Mode=CAN_Activate
PB13.Signal=CAN2_TX
PB14.Mode=Asynchronous
PB14.Signal=USART1_TX
PB15.Mode=Asynchronous
PB15.Signal=USART1_RX
PB6.GPIOParameters=GPIO_Pu
PB6.GPIO_Pu=GPIO_PULLUP
PB6.Mode=I2C
PB6.Signal=I2C1_SCL
PB7.GPIOParameters=GPIO_Pu
PB7.GPIO_Pu=GPIO_PULLUP
PB7.Mode=I2C
PB7.Signal=I2C1_SDA
PB9.GPIOParameters=GPIO_Label
PB9.GPIO_Label=ADC_CLK
PB9.Signal=GPIO_Output
PC10.Mode=Asynchronous
PC10.Signal=USART3_TX
PC11.Mode=Asynchronous
PC11.Signal=USART3_RX
PC14/OSC32_IN.Mode=LSE-External-Oscillator
PC14/OSC32_IN.Signal=RCC_OSC32_IN
PC15/OSC32_OUT.Mode=LSE-External-Oscillator
PC15/OSC32_OUT.Signal=RCC_OSC32_OUT
PC6.Signal=S_TIM3_CH1
PC7.GPIOParameters=GPIO_Label
PC7.GPIO_Label=GPS_INT
PC7.Signal=GPIO_Input
PC9.Mode=I2C
PC9.Signal=I2C3_SDA
PD0.Mode=CAN_Activate
PD0.Signal=CAN1_RX
PD1.Mode=CAN_Activate
PD1.Signal=CAN1_TX
PD3.GPIOParameters=GPIO_Label
PD3.GPIO_Label=LED
PD3.Signal=GPIO_Output
PD6.GPIOParameters=GPIO_PuPd
PD6.GPIO_PuPd=GPIO_NOPULL
PD6.Mode=SD_4_bits_Wide_bus
PD6.Signal=SDMMC2_CK
PD7.GPIOParameters=GPIO_PuPd
PD7.GPIO_PuPd=GPIO_NOPULL
PD7.Mode=SD_4_bits_Wide_bus
PD7.Signal=SDMMC2_CMD
PE10.Mode=CTS_RTS
PE10.Signal=UART7_CTS
PE2.Mode=Full_Duplex_Master
PE2.Signal=SPI4_SCK
PE3.GPIOParameters=GPIO_Label
PE3.GPIO_Label=ADC_DATA_RDY
PE3.Signal=GPIO_Input
PE4.GPIOParameters=GPIO_Label
PE4.GPIO_Label=ADC_CS
PE4.Signal=GPIO_Output
PE5.Mode=Full_Duplex_Master
PE5.Signal=SPI4_MISO
PE6.Mode=Full_Duplex_Master
PE6.Signal=SPI4_MOSI
PE7.Mode=Asynchronous
PE7.Signal=UART7_RX
PE8.Mode=Asynchronous
PE8.Signal=UART7_TX
PE9.Mode=CTS_RTS
PE9.Signal=UART7_RTS
PF14.Mode=I2C
PF14.Signal=I2C4_SCL
PF15.Mode=I2C
PF15.Signal=I2C4_SDA
PF6.Mode=IN4
PF6.Signal=ADC3_IN4
PF7.Mode=IN5
PF7.Signal=ADC3_IN5
PG10.GPIOParameters=GPIO_PuPd
PG10.GPIO_PuPd=GPIO_NOPULL
PG10.Mode=SD_4_bits_Wide_bus
PG10.Signal=SDMMC2_D1
PG11.GPIOParameters=GPIO_PuPd
PG11.GPIO_PuPd=GPIO_NOPULL
PG11.Mode=SD_4_bits_Wide_bus
PG11.Signal=SDMMC2_D2
PG12.GPIOParameters=GPIO_PuPd
PG12.GPIO_PuPd=GPIO_NOPULL
PG12.Mode=SD_4_bits_Wide_bus
PG12.Signal=SDMMC2_D3
PG13.GPIOParameters=GPIO_PuPd,GPIO_Label
PG13.GPIO_Label=SD_DET
PG13.GPIO_PuPd=GPIO_PULLDOWN
PG13.Signal=GPIO_Input
PG5.GPIOParameters=PinState,GPIO_Label
PG5.GPIO_Label=GPS_LNA_EN
PG5.PinState=GPIO_PIN_SET
PG5.Signal=GPIO_Output
PG6.Signal=GPIO_Output
PG9.GPIOParameters=GPIO_PuPd
PG9.GPIO_PuPd=GPIO_NOPULL
PG9.Mode=SD_4_bits_Wide_bus
PG9.Signal=SDMMC2_D0
PH0/OSC_IN.Mode=HSE-External-Oscillator
PH0/OSC_IN.Signal=RCC_OSC_IN
PH1/OSC_OUT.Mode=HSE-External-Oscillator
PH1/OSC_OUT.Signal=RCC_OSC_OUT
RCC.HSE_VALUE=25000000
RCC.SYSCLKFreq_VALUE=216000000
RCC.SYSCLKSource=RCC_SYSCLKSOURCE_PLLCLK
board=custom

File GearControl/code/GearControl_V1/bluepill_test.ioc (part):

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Mcu.Name=STM32F103C(8-B)Tx
Mcu.Package=LQFP48
Mcu.UserName=STM32F103C8Tx
PA0-WKUP.Signal=ADCx_IN0
PA1.Signal=ADCx_IN1
PA10.Signal=S_TIM1_CH3
PA13.Mode=Serial_Wire
PA13.Signal=SYS_JTMS-SWDIO
PA14.Mode=Serial_Wire
PA14.Signal=SYS_JTCK-SWCLK
PA3.GPIOParameters=GPIO_Label
PA3.GPIO_Label=ABS_CLK
PA3.Signal=GPIO_Output
PA4.Signal=ADCx_IN4
PA5.GPIOParameters=GPIO_Label
PA5.GPIO_Label=ABS_CS
PA5.Signal=GPIO_Output
PA6.Signal=ADCx_IN6
PA7.GPIOParameters=GPIO_Label
PA7.GPIO_Label=ABS_DO
PA7.Signal=GPIO_Input
PB11.GPIOParameters=GPIO_Speed,GPIO_PuPd,GPIO_Label
PB11.GPIO_Label=FUEL_CUT
PB11.GPIO_PuPd=GPIO_PULLDOWN
PB11.GPIO_Speed=GPIO_SPEED_FREQ_HIGH
PB11.Signal=GPIO_Output
PB8.Mode=Master
PB8.Signal=CAN_RX
PB9.Mode=Master
PB9.Signal=CAN_TX
PC13-TAMPER-RTC.GPIOParameters=GPIO_PuPd
PC13-TAMPER-RTC.GPIO_PuPd=GPIO_NOPULL
PC13-TAMPER-RTC.Signal=GPIO_Input
PD0-OSC_IN.Mode=HSE-External-Oscillator
PD0-OSC_IN.Signal=RCC_OSC_IN
PD1-OSC_OUT.Mode=HSE-External-Oscillator
PD1-OSC_OUT.Signal=RCC_OSC_OUT
RCC.SYSCLKFreq_VALUE=72000000
RCC.SYSCLKSource=RCC_SYSCLKSOURCE_PLLCLK
board=custom
